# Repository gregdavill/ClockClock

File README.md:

# ClockClock

## Experiements with stepper based instrument dials to create a digitally controlled Analoge Clock.

## Hardware

* MachXo2-640 in QFN48
* Plenty of test pads
* X40 Dual output instument dial stepper (modified for full rotation)
* Hall effect switches for indexing arms on clock
* Flyback diodes on all motor outputs

## Board View

## Schematic

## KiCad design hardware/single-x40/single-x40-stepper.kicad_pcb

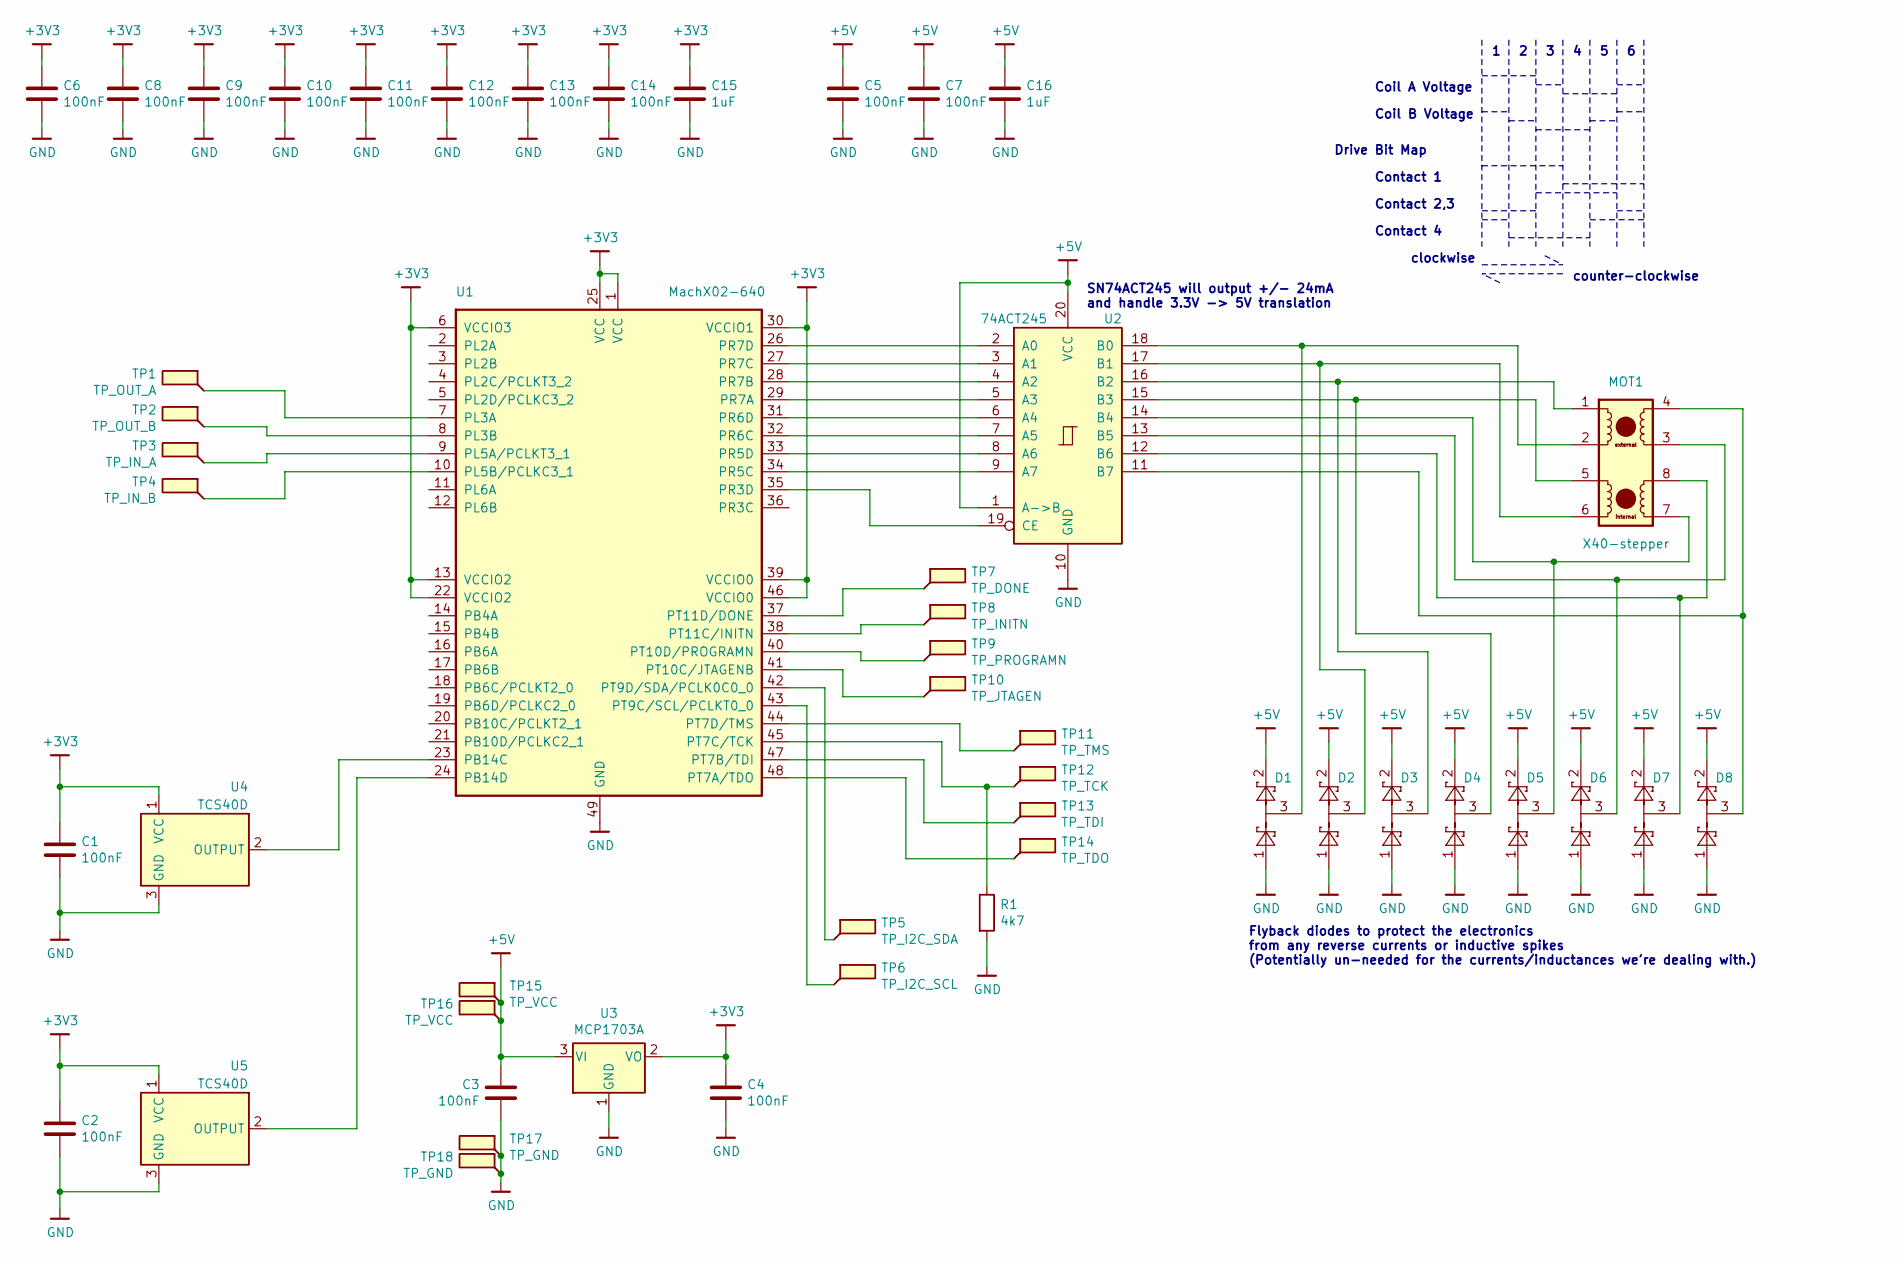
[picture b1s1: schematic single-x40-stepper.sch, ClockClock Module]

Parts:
C1, C2, C3, C4, C5, C6, C7, C8, C9, C10, C11, C12, C13, C14: 100nF; C_0402
C15, C16: 1uF; C_0603
D1, D2, D3, D4, D5, D6, D7, D8: BAT54S; SOT-323_SC-70
MOT1: X40-stepper
R1: 4k7; R_0402
TP1: TP_OUT_A; TestPoint_Pad_D1.0mm
TP2: TP_OUT_B; TestPoint_Pad_D1.0mm
TP3: TP_IN_A; TestPoint_Pad_D1.0mm
TP4: TP_IN_B; TestPoint_Pad_D1.0mm
TP5: TP_I2C_SDA; TestPoint_Pad_D1.0mm
TP6: TP_I2C_SCL; TestPoint_Pad_D1.0mm
TP7: TP_DONE; TestPoint_Pad_D1.0mm
TP8: TP_INITN; TestPoint_Pad_D1.0mm
TP9: TP_PROGRAMN; TestPoint_Pad_D1.0mm
TP10: TP_JTAGEN; TestPoint_Pad_D1.0mm
TP11: TP_TMS; TestPoint_Pad_D1.0mm
TP12: TP_TCK; TestPoint_Pad_D1.0mm
TP13: TP_TDI; TestPoint_Pad_D1.0mm
TP14: TP_TDO; TestPoint_Pad_D1.0mm
TP15, TP16: TP_VCC; TestPoint_Pad_D1.0mm
TP17, TP18: TP_GND; TestPoint_Pad_D1.0mm
U1: MachX02-640; QFN-48-1EP_7x7mm_P0.5mm_EP5.6x5.6mm
U2: 74ACT245; TSSOP-20_4.4x6.5mm_P0.65mm
U3: MCP1703A; SOT-23
U4, U5: TCS40D; SOT-23

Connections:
+3V3: C1.1, C2.1, C4.1, C6.1, C8.1, C9.1, C10.1, C11.1, C12.1, C13.1, C14.1, C15.1, U1.1 (VCC), U1.6 (VCCIO3), U1.13 (VCCIO2), U1.22 (VCCIO2), U1.25 (VCC), U1.30 (VCCIO1), U1.39 (VCCIO0), U1.46 (VCCIO0), U3.2 (VO), U4.1 (VCC), U5.1 (VCC)
+5V: C3.1, C5.1, C7.1, C16.1, D1.2, D2.2, D3.2, D4.2, D5.2, D6.2, D7.2, D8.2, TP15.1, TP16.1, U2.1 (A->B), U2.20 (VCC), U3.3 (VI)
GND: C1.2, C2.2, C3.2, C4.2, C5.2, C6.2, C7.2, C8.2, C9.2, C10.2, C11.2, C12.2, C13.2, C14.2, C15.2, C16.2, D1.1, D2.1, D3.1, D4.1, D5.1, D6.1, D7.1, D8.1, R1.2, TP17.1, TP18.1, U1.49 (GND), U2.10 (GND), U3.1 (GND), U4.3 (GND), U5.3 (GND)
unnamed: D1.3, MOT1.2, U2.18 (B0)
unnamed: D2.3, MOT1.6, U2.17 (B1)
unnamed: D3.3, MOT1.1, U2.16 (B2)
unnamed: D4.3, MOT1.5, U2.15 (B3)
unnamed: D5.3, MOT1.7, U2.14 (B4)
unnamed: D6.3, MOT1.3, U2.13 (B5)
unnamed: D7.3, MOT1.8, U2.12 (B6)
unnamed: D8.3, MOT1.4, U2.11 (B7)
unnamed: R1.1, TP12.1, U1.45 (PT7C/TCK)
unnamed: TP1.1, U1.7 (PL3A)
unnamed: TP2.1, U1.8 (PL3B)
unnamed: TP3.1, U1.9 (PL5A/PCLKT3_1)
unnamed: TP4.1, U1.10 (PL5B/PCLKC3_1)
unnamed: TP5.1, U1.42 (PT9D/SDA/PCLK0C0_0)
unnamed: TP6.1, U1.43 (PT9C/SCL/PCLKT0_0)
unnamed: TP7.1, U1.37 (PT11D/DONE)
unnamed: TP8.1, U1.38 (PT11C/INITN)
unnamed: TP9.1, U1.40 (PT10D/PROGRAMN)
unnamed: TP10.1, U1.41 (PT10C/JTAGENB)
unnamed: TP11.1, U1.44 (PT7D/TMS)
unnamed: TP13.1, U1.47 (PT7B/TDI)
unnamed: TP14.1, U1.48 (PT7A/TDO)
unnamed: U1.23 (PB14C), U4.2 (OUTPUT)
unnamed: U1.24 (PB14D), U5.2 (OUTPUT)
unnamed: U1.26 (PR7D), U2.2 (A0)
unnamed: U1.27 (PR7C), U2.3 (A1)
unnamed: U1.28 (PR7B), U2.4 (A2)
unnamed: U1.29 (PR7A), U2.5 (A3)
unnamed: U1.31 (PR6D), U2.6 (A4)
unnamed: U1.32 (PR6C), U2.7 (A5)
unnamed: U1.33 (PR5D), U2.8 (A6)
unnamed: U1.34 (PR5C), U2.9 (A7)
unnamed: U1.35 (PR3D), U2.19 (CE)

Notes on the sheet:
Coil A Voltage
Coil B Voltage
Drive Bit Map
Contact 1
Contact 2,3
Contact 4
SN74ACT245 will output +/- 24mA and handle 3.3V -> 5V translation
clockwise
counter-clockwise
Flyback diodes to protect the electronics from any reverse currents or inductive spikes (Potentially un-needed for the currents/inductances we're dealing with.)

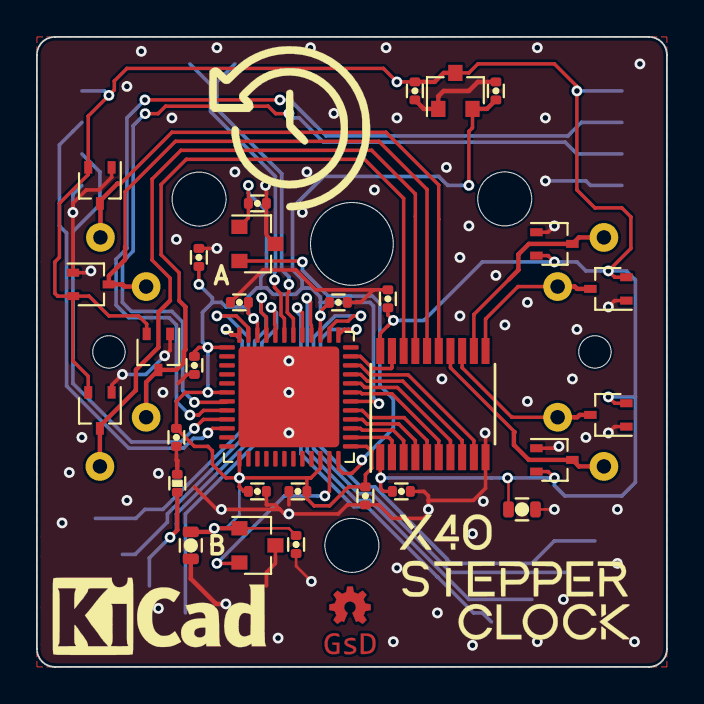
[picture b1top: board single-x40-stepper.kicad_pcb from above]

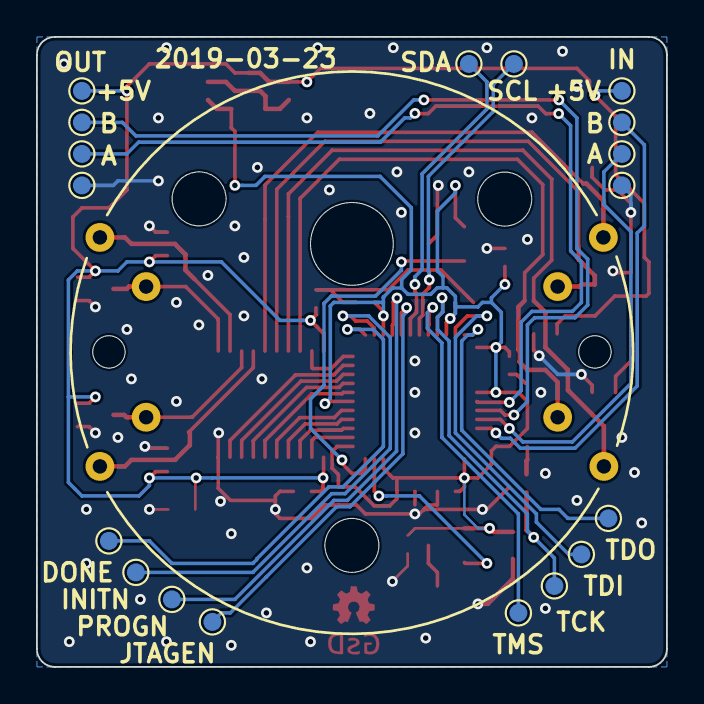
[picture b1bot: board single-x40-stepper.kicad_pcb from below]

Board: 2 copper layers, 35.0 x 35.0 mm, 49 parts (18 on the bottom side), 36 nets.

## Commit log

2019-03-25 Added submodules
2019-03-25 Initial commit of project files
